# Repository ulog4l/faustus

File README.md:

# faustus

32 key [hummingbird](https://github.com/PJE66/hummingbird) adjacent keyboard, also taking inspiration from its variations, such as the [zilpzalp](https://github.com/kilipan/zilpzalp) thumb keys\
also credits to [ergogen](ergogen.cache.works) for simplifying the key placement tremendously\
exclusively supports choc switches, is choc spaced\
exclusively supports the [MIAO](https://github.com/kilipan/miao) controller and [FAK firmware](https://github.com/semickolon/fak)

this keyboard essentially restores the middle column to a hummingbird, making it possible to not combo for these keys and ruin your muscle memory for all other keyboards\
this is made possible by the miao having additional IO pins, removing the 30 key limit of the xiao that is used in the hummingbird

this keyboard uses BAV70 diodes

this pcb has some mounting tabs meant to provide freedom in designing cases, but sticking adhesive feet to the bottom is the lowest profile variant possible and therefore preferred

while i personally have working versions with both hotswap sockets and soldered switches i will of course not take any responsibility for the producteon files being functional, use them at your own risk

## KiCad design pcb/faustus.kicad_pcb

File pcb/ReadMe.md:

provided are the kicad files as well as the scuffed freecad project used to construct the outline of the pcb and the ergogen code to generate the pcb(footprints and such are wrong though, it's just here as a reference)

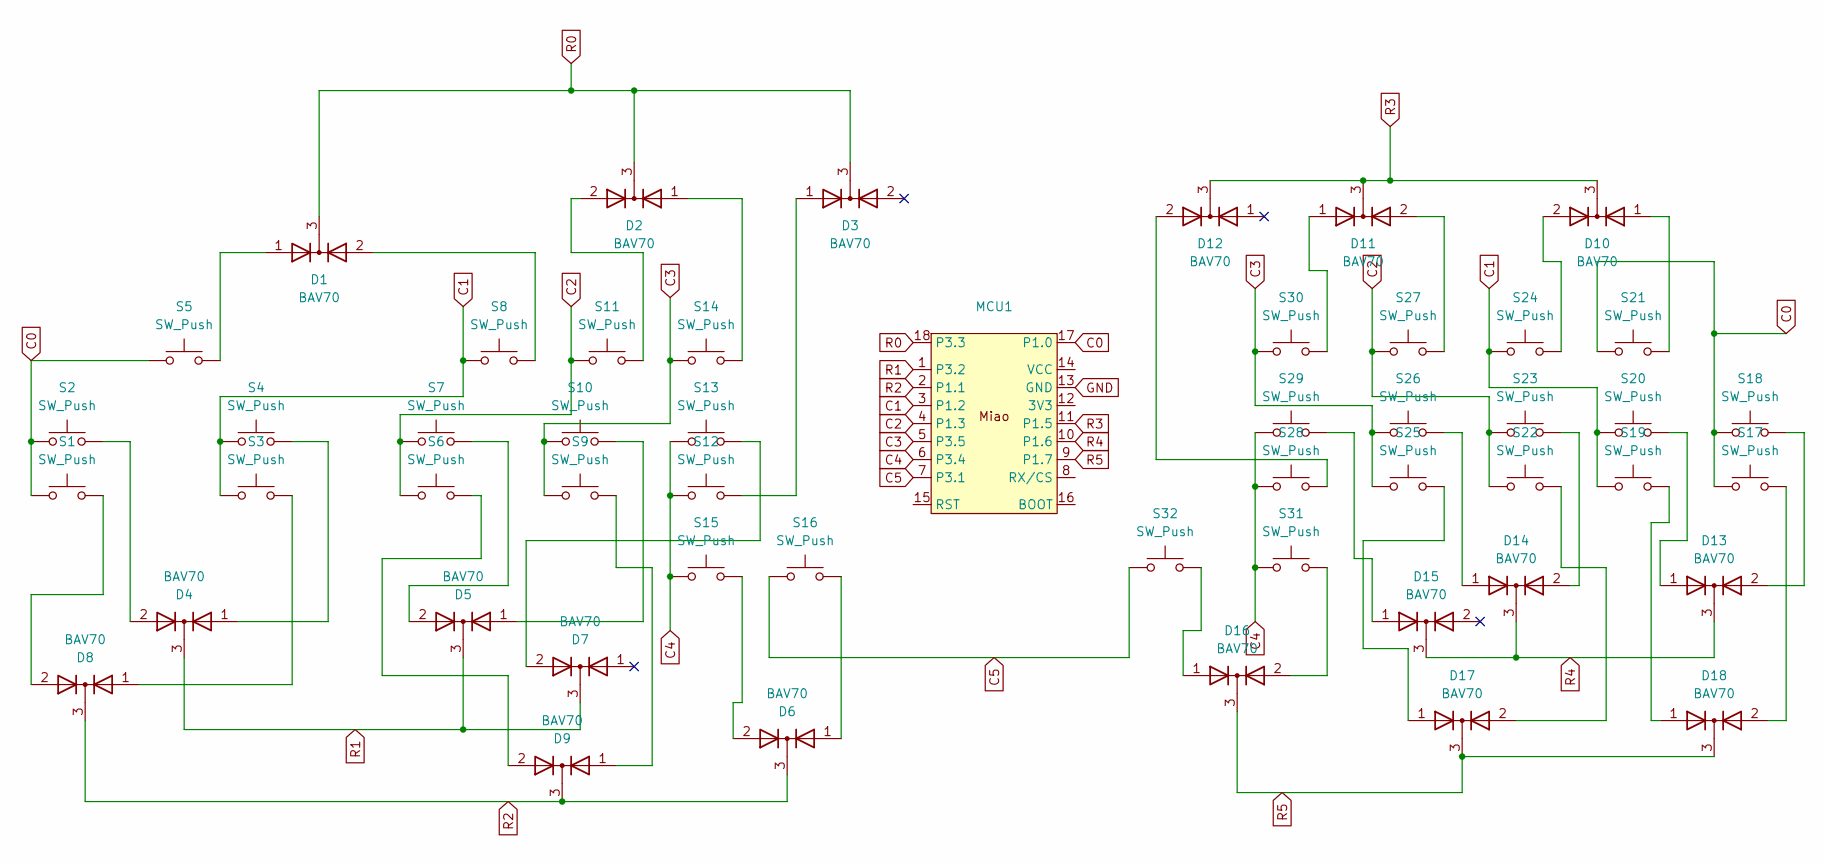
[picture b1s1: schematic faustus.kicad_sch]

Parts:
D1, D2, D3, D4, D5, D6, D7, D8, D9, D10, D11, D12, D13, D14, D15, D16, D17, D18: BAV70; SOT-23_Handsoldering
MCU1: Miao
S1, S2, S3, S4, S5, S6, S7, S8, S9, S10, S11, S12, S13, S14, S15, S16, S17, S18, S19, S20, S21, S22, S23, S24, S25, S26, S27, S28, S29, S30, S31, S32: SW_Push; SW_Kailh_socket_PG1350_optional

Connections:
C0: MCU1.17 (P1.0), S1.1, S2.1, S5.1, S17.1, S18.1, S21.1
C1: MCU1.3 (P1.2), S3.1, S4.1, S8.1, S19.1, S20.1, S24.1
C2: MCU1.4 (P1.3), S6.1, S7.1, S11.1, S22.1, S23.1, S27.1
C3: MCU1.5 (P3.5), S9.1, S10.1, S14.1, S25.1, S26.1, S30.1
C4: MCU1.6 (P3.4), S12.1, S13.1, S15.1, S28.1, S29.1, S31.1
C5: MCU1.7 (P3.1), S16.1, S32.1
GND: MCU1.13 (GND)
unnamed: D1.1 (A), S5.2
unnamed: D1.2 (A), S8.2
unnamed: D2.1 (A), S14.2
unnamed: D2.2 (A), S11.2
unnamed: D3.1 (A), S12.2
unnamed: D4.1 (A), S4.2
unnamed: D4.2 (A), S2.2
unnamed: D5.1 (A), S10.2
unnamed: D5.2 (A), S7.2
unnamed: D6.1 (A), S16.2
unnamed: D6.2 (A), S15.2
unnamed: D7.2 (A), S13.2
unnamed: D8.1 (A), S3.2
unnamed: D8.2 (A), S1.2
unnamed: D9.1 (A), S9.2
unnamed: D9.2 (A), S6.2
unnamed: D10.1 (A), S21.2
unnamed: D10.2 (A), S24.2
unnamed: D11.1 (A), S30.2
unnamed: D11.2 (A), S27.2
unnamed: D12.2 (A), S28.2
unnamed: D13.1 (A), S20.2
unnamed: D13.2 (A), S18.2
unnamed: D14.1 (A), S26.2
unnamed: D14.2 (A), S23.2
unnamed: D15.1 (A), S29.2
unnamed: D16.1 (A), S32.2
unnamed: D16.2 (A), S31.2
unnamed: D17.1 (A), S25.2
unnamed: D17.2 (A), S22.2
unnamed: D18.1 (A), S19.2
unnamed: D18.2 (A), S17.2
R0: D1.3 (K), D2.3 (K), D3.3 (K), MCU1.18 (P3.3)
R1: D4.3 (K), D5.3 (K), D7.3 (K), MCU1.1 (P3.2)
R2: D6.3 (K), D8.3 (K), D9.3 (K), MCU1.2 (P1.1)
R3: D10.3 (K), D11.3 (K), D12.3 (K), MCU1.11 (P1.5)
R4: D13.3 (K), D14.3 (K), D15.3 (K), MCU1.10 (P1.6)
R5: D16.3 (K), D17.3 (K), D18.3 (K), MCU1.9 (P1.7)

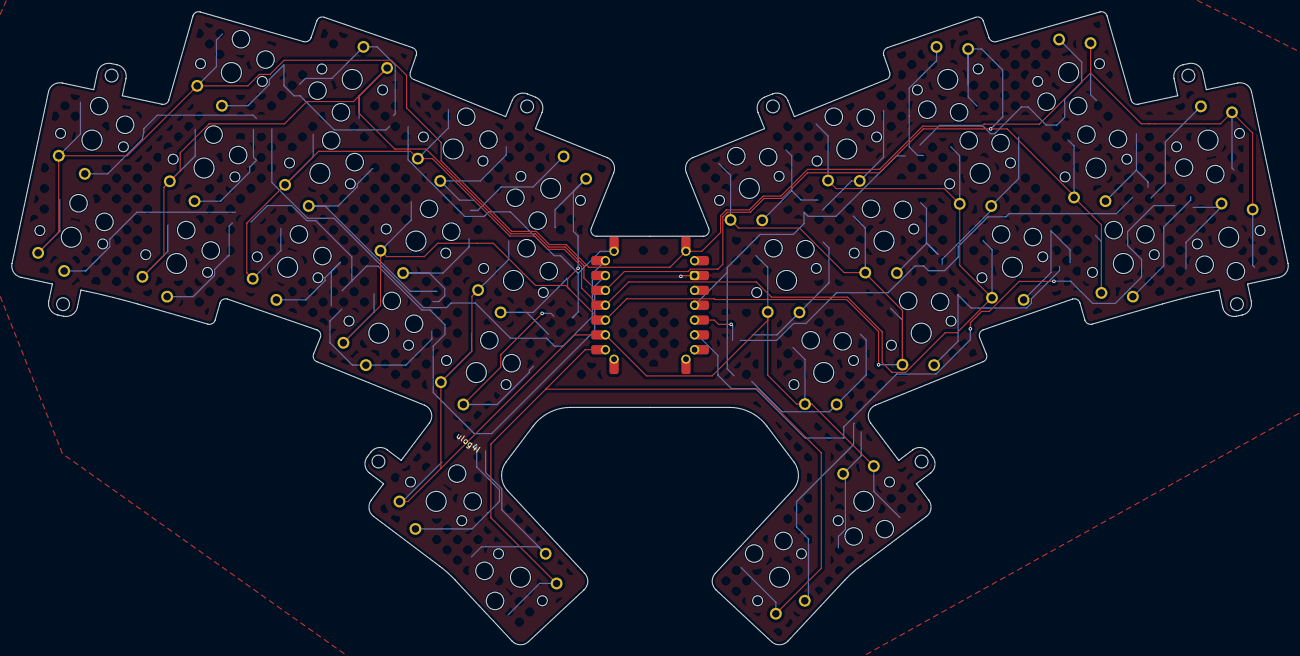
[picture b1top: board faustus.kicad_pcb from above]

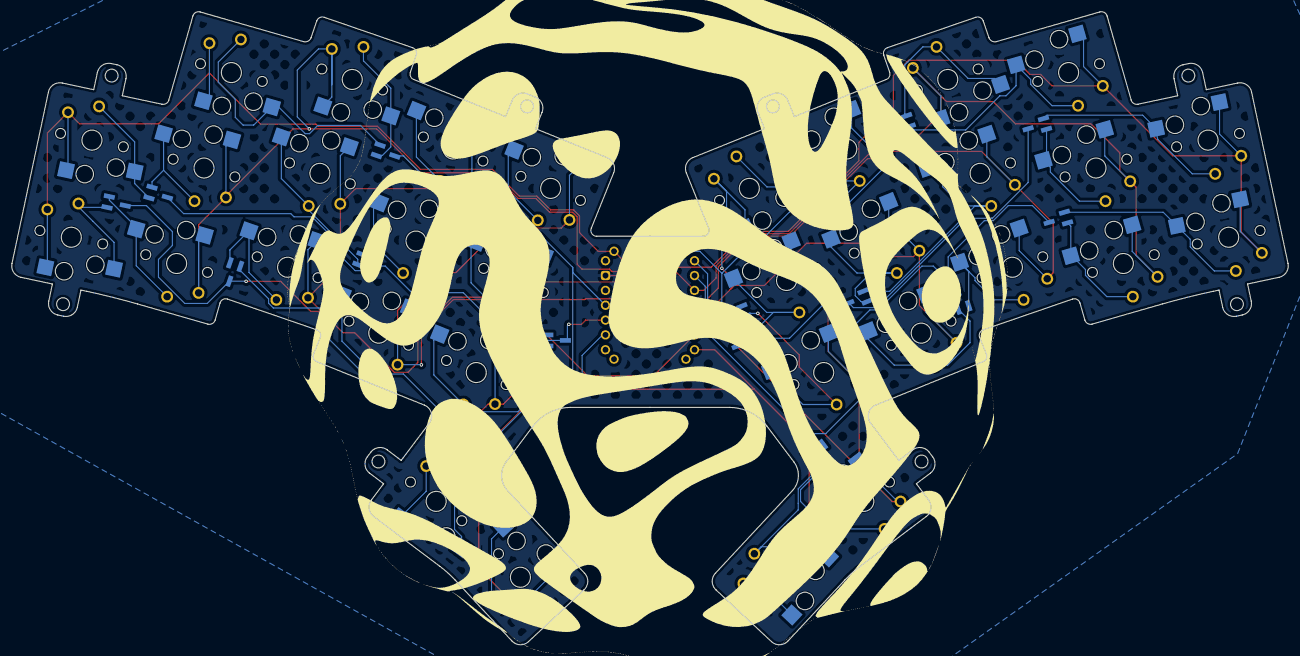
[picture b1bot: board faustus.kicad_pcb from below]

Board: 2 copper layers, 218.5 x 108.4 mm, 51 parts (18 on the bottom side), 44 nets.

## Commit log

2025-02-21 add stuff
